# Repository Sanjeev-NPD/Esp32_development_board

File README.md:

# Esp32_development_board
This file includes the schematic, board and gerber file of the pcb. Tested product.

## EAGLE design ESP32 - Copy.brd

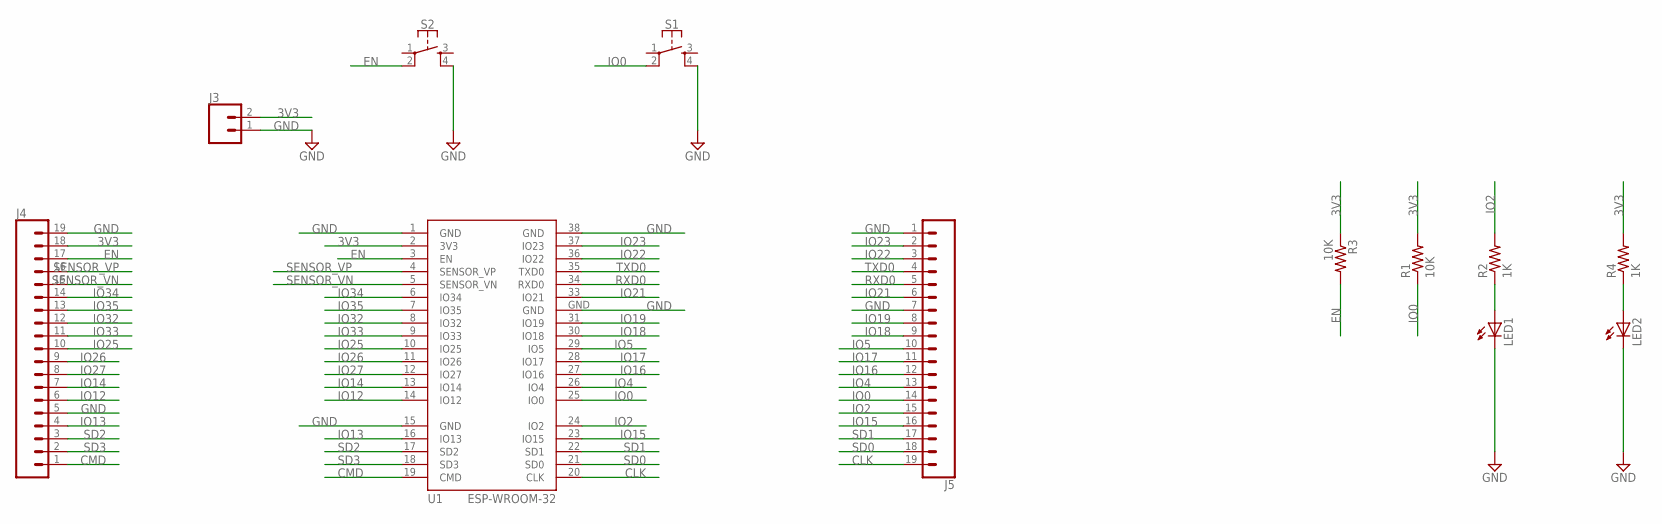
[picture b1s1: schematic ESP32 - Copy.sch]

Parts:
J3: CONN_02; 1X02
J4, J5: CONN_191X19_NO_SILK; 1X19_NO_SILK
LED1, LED2: LED5MM
R1, R3: 10K; 0207/10
R2, R4: 1K; 0207/10
S1, S2: MOMENTARY-SWITCH-SPST-2-SMD-5.2MM-TALL; TACTILE_SWITCH_SMD_5.2MM
U1: ESP-WROOM-32

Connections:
3V3: J3.2, J4.18, R1.2, R3.1, R4.2, U1.2 (3V3)
CLK: J5.19, U1.20 (CLK)
CMD: J4.1, U1.19 (CMD)
EN: J4.17, R3.2, S2.2, U1.3 (EN)
GND: J3.1, J4.5, J4.19, J5.1, J5.7, LED1.K (C), LED2.K (C), S1.4, S2.4, U1.1 (GND), U1.15 (GND), U1.38 (GND), U1.GND
IO0: J5.14, R1.1, S1.2, U1.25 (IO0)
IO2: J5.15, R2.2, U1.24 (IO2)
IO4: J5.13, U1.26 (IO4)
IO5: J5.10, U1.29 (IO5)
IO12: J4.6, U1.14 (IO12)
IO13: J4.4, U1.16 (IO13)
IO14: J4.7, U1.13 (IO14)
IO15: J5.16, U1.23 (IO15)
IO16: J5.12, U1.27 (IO16)
IO17: J5.11, U1.28 (IO17)
IO18: J5.9, U1.30 (IO18)
IO19: J5.8, U1.31 (IO19)
IO21: J5.6, U1.33 (IO21)
IO22: J5.3, U1.36 (IO22)
IO23: J5.2, U1.37 (IO23)
IO25: J4.10, U1.10 (IO25)
IO26: J4.9, U1.11 (IO26)
IO27: J4.8, U1.12 (IO27)
IO32: J4.12, U1.8 (IO32)
IO33: J4.11, U1.9 (IO33)
IO34: J4.14, U1.6 (IO34)
IO35: J4.13, U1.7 (IO35)
unnamed: LED1.A, R2.1
unnamed: LED2.A, R4.1
RXD0: J5.5, U1.34 (RXD0)
SD0: J5.18, U1.21 (SD0)
SD1: J5.17, U1.22 (SD1)
SD2: J4.3, U1.17 (SD2)
SD3: J4.2, U1.18 (SD3)
SENSOR_VN: J4.15, U1.5 (SENSOR_VN)
SENSOR_VP: J4.16, U1.4 (SENSOR_VP)
TXD0: J5.4, U1.35 (TXD0)

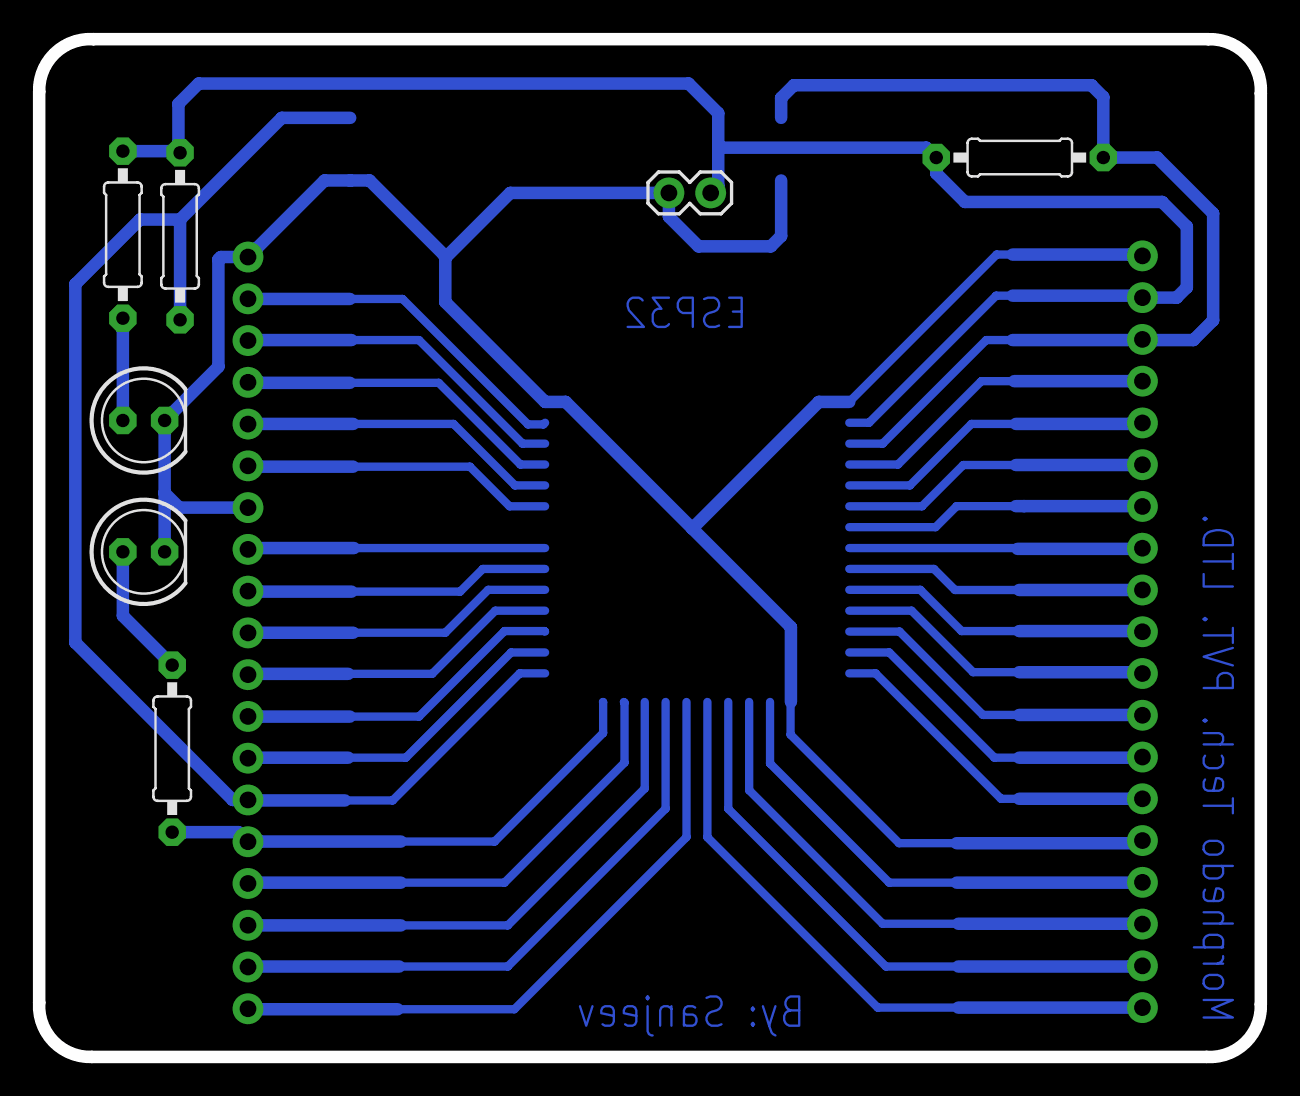
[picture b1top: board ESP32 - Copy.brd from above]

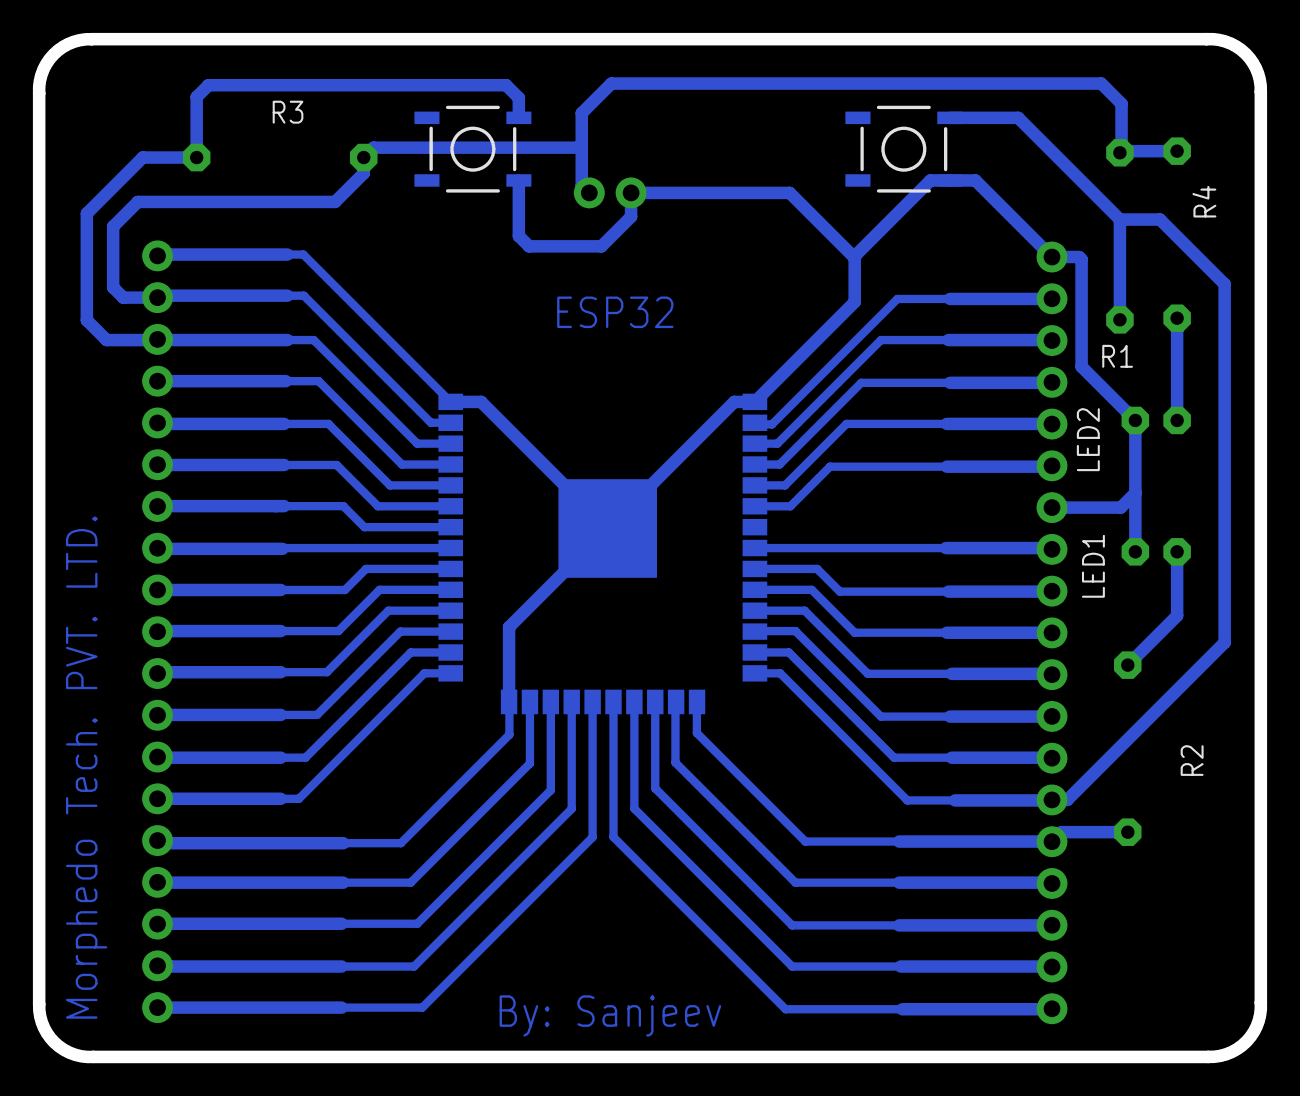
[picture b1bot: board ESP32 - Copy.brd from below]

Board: 2 copper layers, 74.3 x 61.9 mm, 12 parts (3 on the bottom side), 37 nets.

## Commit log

2024-07-16 enter

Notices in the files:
parts and their libraries:
SparkFun-Connectors: Licensing: Creative Commons ShareAlike 4.0 International - https://creativecommons.org/licenses/by-sa/4.0
ESP32: Creative Commons Attribution-ShareAlike 4.0 International
